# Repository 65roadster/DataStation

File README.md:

# DataStation
Ryan's Data Station

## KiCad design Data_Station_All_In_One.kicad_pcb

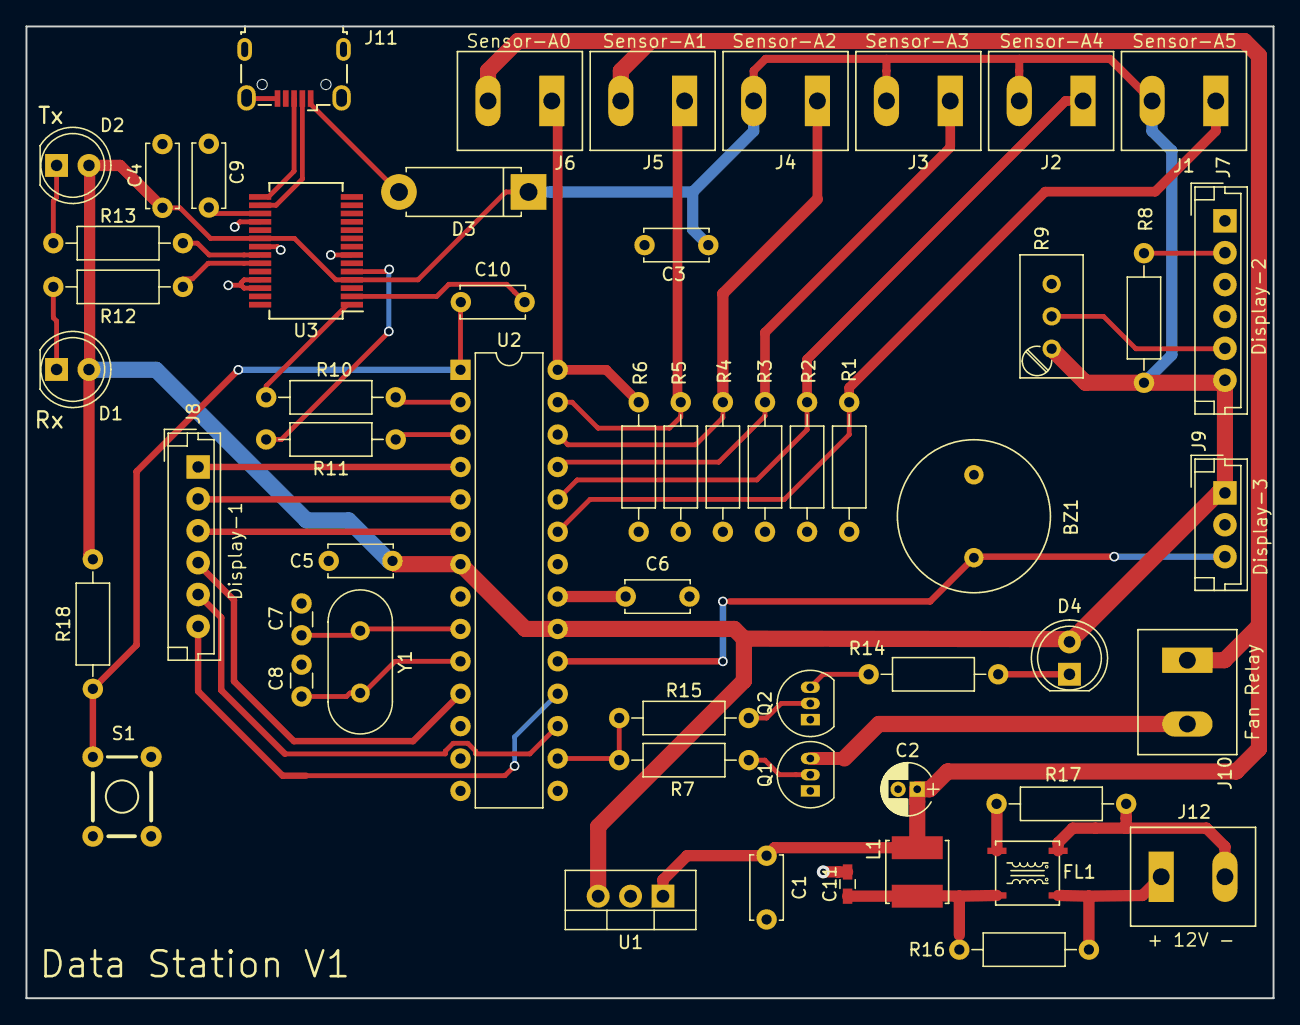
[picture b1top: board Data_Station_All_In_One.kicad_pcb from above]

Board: 2 copper layers, 97.8 x 76.2 mm, 55 parts (0 on the bottom side), 44 nets.

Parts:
BZ1: Buzzer; Buzzer-WT-1212
C1: 0.33; C_Disc_D5.0mm_W2.5mm_P5.00mm
C2: 10u; CP_Radial_D4.0mm_P1.50mm
C3, C4, C5, C6: 0.1; C_Disc_D5.0mm_W2.5mm_P5.00mm
C7, C8: 18p; C_Disc_D3.0mm_W1.6mm_P2.50mm
C9, C10: 0.1u; C_Disc_D5.0mm_W2.5mm_P5.00mm
C11: 1U; C_0603_HandSoldering
D1, D2, D4: LED; LED_D5.0mm
D3: 1N4002; D_5W_P10.16mm_Horizontal
FL1: EMI_Filter_CommonMode; Choke-Muarata-PLT5BPH5013R1SN#
J1, J2, J3, J4, J5, J6, J10, J12: Conn_01x02_Male; Ryans_Terminal_Block_10mm7.75mmP5mm
J7, J8: Conn_01x06_Male; JST_EH_B06B-EH-A_06x2.50mm_Straight
J9: Conn_01x03_Male; JST_EH_B03B-EH-A_03x2.50mm_Straight
J11: USB_B_Micro; USB_Micro-B_Wuerth-629105150521
L1: L; Inductor-Taiyo-Yuden-NRS5020T4R7MMGJ
Q1, Q2: 2N2222; TO-92_Inline_Narrow_Oval
R1, R2, R3, R4: 10k; R_Axial_DIN0207_L6.3mm_D2.5mm_P10.16mm_Horizontal
R5, R6, R8, R14: 220; R_Axial_DIN0207_L6.3mm_D2.5mm_P10.16mm_Horizontal
R7: 2.2k; R_Axial_DIN0207_L6.3mm_D2.5mm_P10.16mm_Horizontal
R9: 10k; Potentiometer_Trimmer_Bourns_3296W
R10, R11, R12, R13, R18: 1k; R_Axial_DIN0207_L6.3mm_D2.5mm_P10.16mm_Horizontal
R15: 4.7k; R_Axial_DIN0207_L6.3mm_D2.5mm_P10.16mm_Horizontal
R16, R17: 0; R_Axial_DIN0207_L6.3mm_D2.5mm_P10.16mm_Horizontal
S1: Momentary_Push_Buttom_KM_6x6; Momentary_Push_Button_KM_6x6
U1: LM7805_TO220; TO-220-3_Vertical
U2: ATMEGA328P-PU; DIP-28_W7.62mm
U3: FT232RL; SSOP-28_5.3x10.2mm_Pitch0.65mm
Y1: Crystal; Crystal_HC49-U_Vertical

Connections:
+5V: C3.1, C4.1, C5.1, D1.2, D2.2, D3.1, D4.2, J1.2, J2.2, J3.2, J4.2, J7.6, J9.1, R8.2, R9.1, R18.2, U1.3, U2.7, U2.20, U3.4, U3.20
+12V: C1.1, C2.1, J5.2, J6.2, J10.1, L1.2, U1.1
A0: J1.1, R1.1, U2.23
A1: J2.1, R2.1, U2.24
A2: J3.1, R3.1, U2.25
A3: J4.1, R4.1, U2.26
A4: J5.1, R5.1, U2.27
A5: J6.1, R6.1, U2.28
D0: R10.2, U2.2
D1: R11.2, U2.3
D2: J8.1, U2.4
D3: J8.2, U2.5
D4: J8.3, U2.6
D5: J8.4, U2.11
D10: R7.2, R15.2, U2.16
D11: J8.5, U2.17
D12: J8.6, U2.18
D13: BZ1.1, J9.3, U2.19
GND: BZ1.2, C1.2, C2.2, C3.2, C4.2, C5.2, C6.2, C7.1, C8.1, C9.1, C11.2, FL1.3, J7.1, J7.3, J7.4, J9.2, J11.5, J11.6, Q1.1, Q2.1, R1.2, R2.2, R3.2, R4.2, R5.2, R6.2, R9.3, R17.1, S1.2, U1.2, U2.8, U2.22, U3.7, U3.18, U3.21, U3.25, U3.26
unnamed: C6.1, U2.21
unnamed: C7.2, U2.9, Y1.1
unnamed: C8.2, U2.10, Y1.2
unnamed: C9.2, U3.17
unnamed: C10.2, U3.2
unnamed: C11.1, FL1.2, L1.1, R16.1
unnamed: D1.1, R12.2
unnamed: D2.1, R13.2
unnamed: D3.2, J11.1
unnamed: D4.1, R14.2
unnamed: FL1.1, J12.1, R16.2
unnamed: FL1.4, J12.2, R17.2
unnamed: J7.2, R8.1
unnamed: J7.5, R9.2
unnamed: J10.2, Q1.3
unnamed: J11.2, U3.16
unnamed: J11.3, U3.15
unnamed: Q1.2, R7.1
unnamed: Q2.2, R15.1
unnamed: Q2.3, R14.1
unnamed: R12.1, U3.23
unnamed: R13.1, U3.22
RESET: C10.1, R18.1, S1.1, U2.1
RX: R10.1, U3.1
TX: R11.1, U3.5

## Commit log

2020-01-09 Moved USB Micro to PCB Edge
2020-01-19 updated to reflect actual order
